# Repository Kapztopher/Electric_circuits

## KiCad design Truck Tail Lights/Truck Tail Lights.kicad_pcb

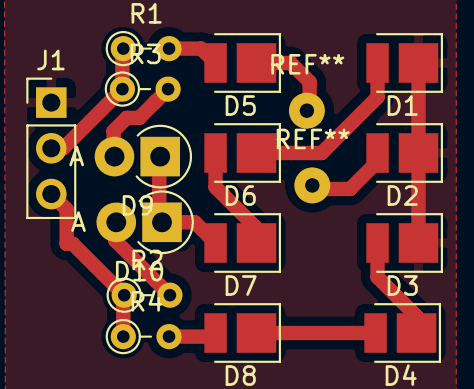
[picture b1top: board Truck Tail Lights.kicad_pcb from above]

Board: 2 copper layers, 15 parts (0 on the bottom side), 13 nets.

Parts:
D1, D2, D5, D6, D7: RED; LED_PLCC_2835
D3, D4, D8: WHITE; LED_PLCC_2835
D9, D10: D; D_DO-41_SOD81_P2.54mm_Vertical_AnodeUp
J1: Gnd Brakes Parkers; PinHeader_1x03_P2.54mm_Vertical
R1, R2, R3, R4: R_Small; R_Axial_DIN0204_L3.6mm_D1.6mm_P2.54mm_Vertical

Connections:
/BrakesLights: J1.2, R1.1, R3.1
/ParkerLights: J1.3, R2.1, R4.1
GND: D1.1, D2.1, D3.1, J1.1
unnamed: D1.2, D6.1
unnamed: D2.2, D5.1
unnamed: D3.2, D4.1
unnamed: D4.2, D8.1
unnamed: D5.2, R1.2
unnamed: D6.2, D7.1
unnamed: D8.2, R4.2
unnamed: D9.2, R3.2
unnamed: D7.2, D9.1, D10.1
unnamed: D10.2, R2.2
